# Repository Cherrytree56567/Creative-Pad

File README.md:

# Creative Pad
A simple Macropad which has Hotswap Kailh Switches with custom key binds.

## Features
 - Hotswap Kailh Switches
 - MX Switches
 - RP2040
 - LCD Screen
 - FPC Connector

## Goals
 - Proper support with Ableton

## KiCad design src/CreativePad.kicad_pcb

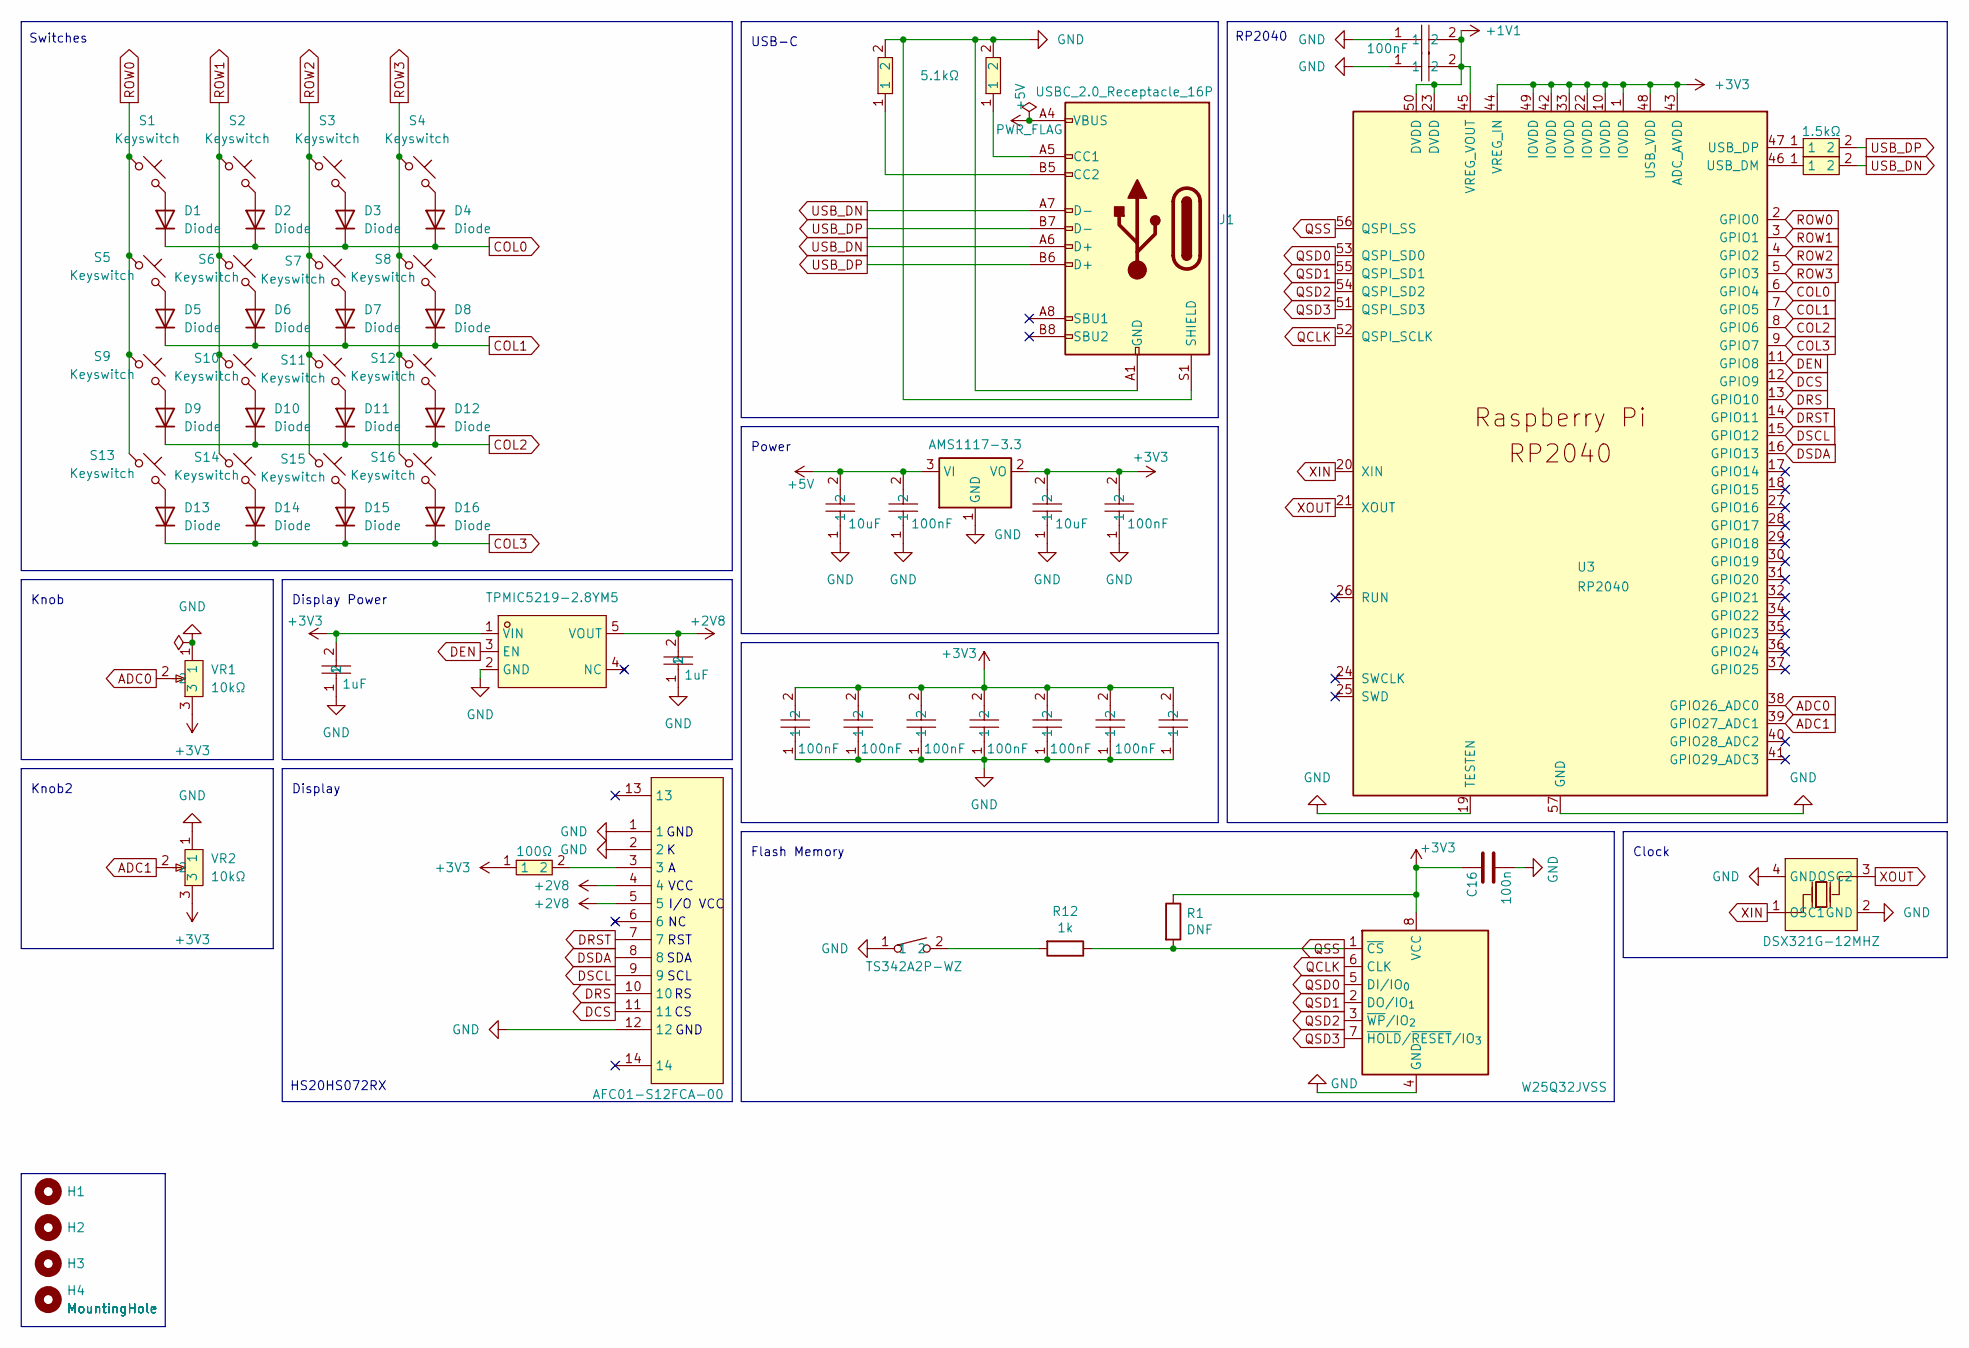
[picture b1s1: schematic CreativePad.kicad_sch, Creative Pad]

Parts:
C1, C4: 10uF; C0603; LCSC Part C1691
C2, C3, C5, C6, C7, C8, C9, C10, C13, C14, C17: 100nF; C0603; LCSC Part C14663
C12, C15: 1uF; C0402; LCSC Part C14445
C16: 100n; C_0402_1005Metric
D1, D2, D3, D4, D5, D6, D7, D8, D9, D10, D11, D12, D13, D14, D15, D16: Diode; Diode_DO-35
FPC1: AFC01-S12FCA-00; FPC-SMD_AFC01-S12FCA-00; LCSC Part C262661
H1, H2, H3, H4: MountingHole; MountingHole_2.2mm_M2
J1: USBC_2.0_Receptacle_16P; USB_C_Receptacle_HCTL_HC-TYPE-C-16P-01A
R1: DNF; R_0402_1005Metric
R2, R6: 1.5kΩ; R0603; LCSC Part C2907083
R4, R9: 5.1kΩ; R0603; LCSC Part C105580
R8: 100Ω; R0402; LCSC Part C25076
R12: 1k; R_0402_1005Metric
S1, S2, S3, S4, S5, S6, S7, S8, S9, S10, S11, S12, S13, S14, S15, S16: Keyswitch; SW_Hotswap_Kailh_MX_1.00u
SW1: TS342A2P-WZ; SW-SMD_L4.0-W2.9-LS5.0; LCSC Part C557591
U1: TPMIC5219-2.8YM5; SOT-23-5_L2.9-W1.6-P0.95-LS2.8-BR; LCSC Part C18212650
U2: AMS1117-3.3; SOT-223-3_TabPin2
U3: RP2040; RP2040-QFN-56
U5: W25Q32JVSS; SOIC-8_5.3x5.3mm_P1.27mm
VR1, VR2: 10kΩ; RES-ADJ-TH_3362P; LCSC Part C58159
X2: DSX321G-12MHZ; CRYSTAL-SMD_4P-L3.2-W2.5-BL; LCSC Part C93234

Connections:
+1V1: C13.2, C17.2, U3.23 (DVDD), U3.45 (VREG_VOUT), U3.50 (DVDD)
+2V8: C12.2, FPC1.4, FPC1.5, U1.5 (VOUT)
+3V3: C3.2, C4.2, C5.2, C6.2, C7.2, C8.2, C9.2, C10.2, C14.2, C15.2, C16.1, R1.1, R8.1, U1.1 (VIN), U2.2 (VO), U3.1 (IOVDD), U3.10 (IOVDD), U3.22 (IOVDD), U3.33 (IOVDD), U3.42 (IOVDD), U3.43 (ADC_AVDD), U3.44 (VREG_IN), U3.48 (USB_VDD), U3.49 (IOVDD), U5.8 (VCC), VR1.3, VR2.3
+5V: C1.2, C2.2, J1.A4 (VBUS), J1.A9 (VBUS), J1.B4 (VBUS), J1.B9 (VBUS), U2.3 (VI)
ADC0: U3.38 (GPIO26_ADC0), VR1.2
ADC1: U3.39 (GPIO27_ADC1), VR2.2
COL0: D1.1 (K), D2.1 (K), D3.1 (K), D4.1 (K), U3.6 (GPIO4)
COL1: D5.1 (K), D6.1 (K), D7.1 (K), D8.1 (K), U3.7 (GPIO5)
COL2: D9.1 (K), D10.1 (K), D11.1 (K), D12.1 (K), U3.8 (GPIO6)
COL3: D13.1 (K), D14.1 (K), D15.1 (K), D16.1 (K), U3.9 (GPIO7)
DCS: FPC1.11, U3.12 (GPIO9)
DEN: U1.3 (EN), U3.11 (GPIO8)
DRS: FPC1.10, U3.13 (GPIO10)
DRST: FPC1.7, U3.14 (GPIO11)
DSCL: FPC1.9, U3.15 (GPIO12)
DSDA: FPC1.8, U3.16 (GPIO13)
GND: C1.1, C2.1, C3.1, C4.1, C5.1, C6.1, C7.1, C8.1, C9.1, C10.1, C12.1, C13.1, C14.1, C15.1, C16.2, C17.1, FPC1.1, FPC1.2, FPC1.12, J1.A1 (GND), J1.A12 (GND), J1.B1 (GND), J1.B12 (GND), J1.S1 (SHIELD), R4.2, R9.2, SW1.1, U1.2 (GND), U2.1 (GND), U3.19 (TESTEN), U3.57 (GND), U5.4 (GND), VR1.1, VR2.1, X2.2 (GND), X2.4 (GND)
unnamed: D1.2 (A), S1.2
unnamed: D2.2 (A), S2.2
unnamed: D3.2 (A), S3.2
unnamed: D4.2 (A), S4.2
unnamed: D5.2 (A), S5.2
unnamed: D6.2 (A), S6.2
unnamed: D7.2 (A), S7.2
unnamed: D8.2 (A), S8.2
unnamed: D9.2 (A), S9.2
unnamed: D10.2 (A), S10.2
unnamed: D11.2 (A), S11.2
unnamed: D12.2 (A), S12.2
unnamed: D13.2 (A), S13.2
unnamed: D14.2 (A), S14.2
unnamed: D15.2 (A), S15.2
unnamed: D16.2 (A), S16.2
unnamed: FPC1.3, R8.2
unnamed: J1.A5 (CC1), R9.1
unnamed: J1.B5 (CC2), R4.1
unnamed: R12.2, SW1.2
unnamed: R6.1, U3.46 (USB_DM)
unnamed: R2.1, U3.47 (USB_DP)
QCLK: U3.52 (QSPI_SCLK), U5.6 (CLK)
QSD0: U3.53 (QSPI_SD0), U5.5 (DI/IO_{0})
QSD1: U3.55 (QSPI_SD1), U5.2 (DO/IO_{1})
QSD2: U3.54 (QSPI_SD2), U5.3 (~WP/IO_{2})
QSD3: U3.51 (QSPI_SD3), U5.7 (~HOLD/~RESET/IO_{3})
QSS: R1.2, R12.1, U3.56 (QSPI_SS), U5.1 (~CS)
ROW0: S1.1, S5.1, S9.1, S13.1, U3.2 (GPIO0)
ROW1: S2.1, S6.1, S10.1, S14.1, U3.3 (GPIO1)
ROW2: S3.1, S7.1, S11.1, S15.1, U3.4 (GPIO2)
ROW3: S4.1, S8.1, S12.1, S16.1, U3.5 (GPIO3)
USB_DN: J1.A6 (D+), J1.A7 (D-), R6.2
USB_DP: J1.B6 (D+), J1.B7 (D-), R2.2
XIN: U3.20 (XIN), X2.1 (OSC1)
XOUT: U3.21 (XOUT), X2.3 (OSC2)

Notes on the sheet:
VCC
GND
I/O VCC
Knob
HS20HS072RX
Switches
Display
Display Power
Power
Knob2
SCL
RP2040
Flash Memory
USB-C
RST
SDA
Clock

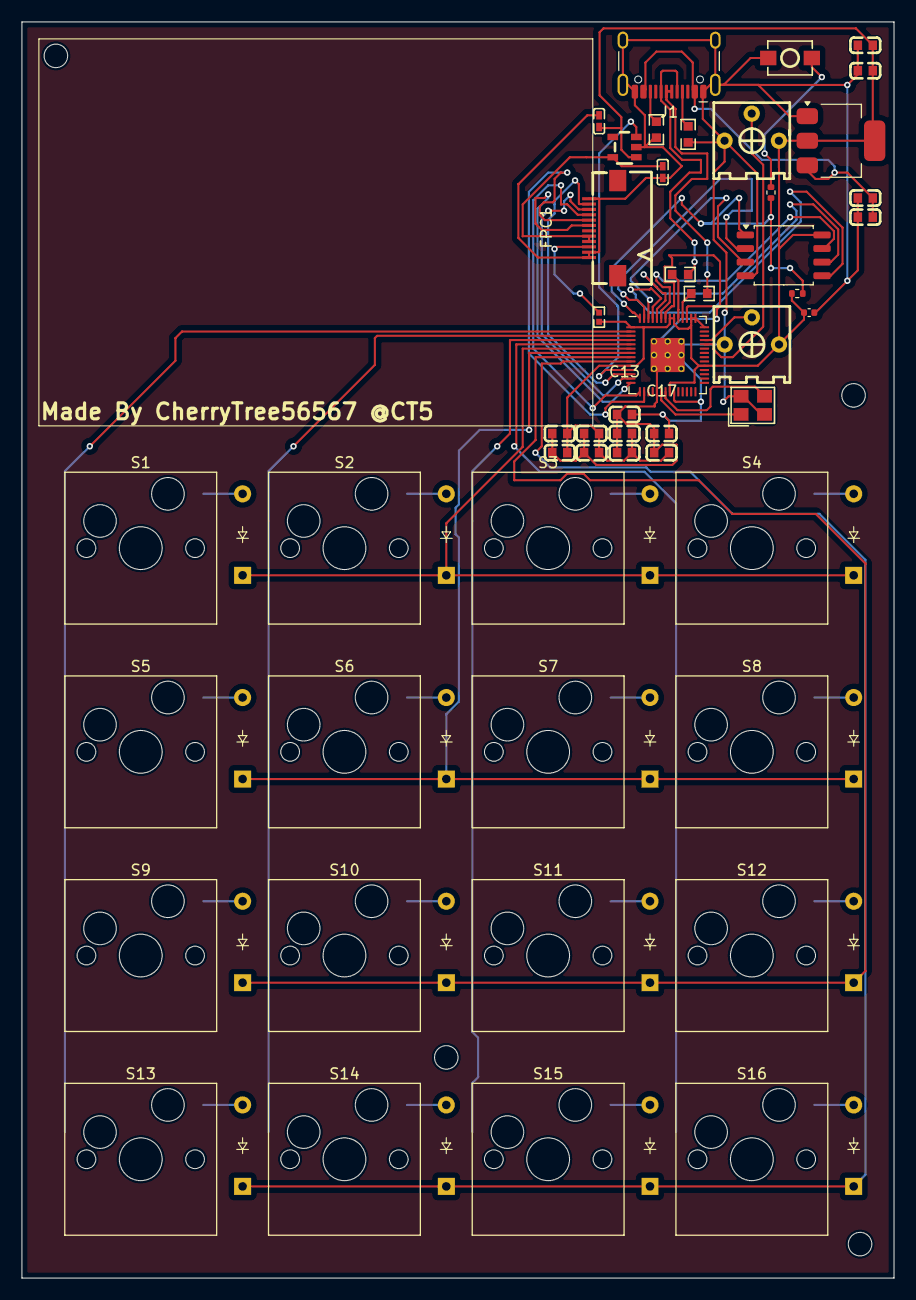
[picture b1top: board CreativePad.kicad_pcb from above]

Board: 2 copper layers, 81.6 x 117.5 mm, 69 parts (0 on the bottom side), 53 nets.

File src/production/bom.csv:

Designator,Footprint,Quantity,Value,LCSC Part #
"C1, C4",C0603,2,10uF,C1691
"C10, C13, C14, C17, C2, C3, C5, C6, C7, C8, C9",C0603,11,100nF,C14663
"C12, C15",C0402,2,1uF,C14445
C16,0402,1,100n,
"D1, D10, D11, D12, D13, D14, D15, D16, D2, D3, D4, D5, D6, D7, D8, D9",Diode_DO-35,16,Diode,
FPC1,FPC-SMD_AFC01-S12FCA-00,1,AFC01-S12FCA-00,C262661
J1,USB_C_Receptacle_HCTL_HC-TYPE-C-16P-01A,1,USBC_2.0_Receptacle_16P,
R1,0402,1,DNF,
R12,0402,1,1k,
"R2, R6",R0603,2,1.5kΩ,C2907083
"R4, R9",R0603,2,5.1kΩ,C105580
R8,R0402,1,100Ω,C25076
"S1, S10, S11, S12, S13, S14, S15, S16, S2, S3, S4, S5, S6, S7, S8, S9",SW_Hotswap_Kailh_MX_1.00u,16,Keyswitch,
SW1,SW-SMD_L4.0-W2.9-LS5.0,1,TS342A2P-WZ,C557591
U1,SOT-23-5_L2.9-W1.6-P0.95-LS2.8-BR,1,TPMIC5219-2.8YM5,C18212650
U2,SOT-223-3_TabPin2,1,AMS1117-3.3,
U3,RP2040-QFN-56,1,RP2040,
U5,SOIC-8_5.3x5.3mm_P1.27mm,1,W25Q32JVSS,
"VR1, VR2",RES-ADJ-TH_3362P,2,10kΩ,C58159
X2,CRYSTAL-SMD_4P-L3.2-W2.5-BL,1,DSX321G-12MHZ,C93234

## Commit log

2025-07-31 Added Journal
2025-08-01 Day 2
2025-08-02 Day 3
2025-08-03 Day 3-4
2025-08-03 Day 5 - P1
2025-08-04 Day 5
2025-08-04 Day 5 - Part 2
2025-08-06 Day 6
2025-08-07 Day 8
2025-08-07 Day 8 - Part 2
2025-08-07 Added 3D Model
2025-08-07 Fixed Model (FPC)
2025-08-08 Day 9
2025-08-09 Day 10
2025-08-10 Day 11
2025-08-11 Day 12
2025-08-15 Day 13 - 14
2025-08-28 Added STL
